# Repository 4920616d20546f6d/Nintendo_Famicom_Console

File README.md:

# Goals
This project documents the Nintendo Family Computer from Japan. The goal is to provide complete, verified, schematics and PCB for every version of the console and essential accessories.

# Progress
- December 1, HVC-CPU-GPM-02 all footprints reviewed. Holes and pads corrected. Revision uploaded.
- November 30, HVC-CPU-GPM-02 verified to be electrically correct. There are 3 mechanical errors. The drill sizes for the 15 pin connector, TC1, and Reset switch are too small. Drills and annulus will be adjusted in next revision.
- November 27, HVC-CPU-07 acquired
- November 12, 2025 the HVC-CPU-GPM-02 mainboard was sent out for manufacturing.
- November 10, 2025 the first versions of all essential hardware and accessories have been complete and added to the repository.

# Project Status
## Console HVC-001
| Revision | Schematic | Symbols | Datasheets | Notes | PCB | Footprint | Pads | Masks | Text | Graphics | Models | Photos | Ready for Manufacturer | Manufactured |
|----------|-----------|---------|------------|-------|-----|-----------|------|-------|------|----------|--------|--------|------------------------|--------------|
| HVC-CPU | ❌ | ❌ | ❌ | ❌ | ❌ | ❌ | ❌ | ❌ | ❌ | ❌ | ❌ | ❌ | ❌ | ❌ |
| HVC-CPU-02 | ❌ | ❌ | ❌ | ❌ | ❌ | ❌ | ❌ | ❌ | ❌ | ❌ | ❌ | ❌ | ❌ | ❌ |
| HVC-CPU-03 | ❌ | ❌ | ❌ | ❌ | ❌ | ❌ | ❌ | ❌ | ❌ | ❌ | ❌ | ❌ | ❌ | ❌ |
| HVC-CPU-04 | ❌ | ❌ | ❌ | ❌ | ❌ | ❌ | ❌ | ❌ | ❌ | ❌ | ❌ | ❌ | ❌ | ❌ |
| HVC-CPU-05 | ❌ | ❌ | ❌ | ❌ | ❌ | ❌ | ❌ | ❌ | ❌ | ❌ | ❌ | ❌ | ❌ | ❌ |
| HVC-CPU-06 | ❌ | ❌ | ❌ | ❌ | ❌ | ❌ | ❌ | ❌ | ❌ | ❌ | ❌ | ❌ | ❌ | ❌ |
| HVC-CPU-07 | ❌ | ❌ | ❌ | ❌ | ❌ | ❌ | ❌ | ❌ | ❌ | ❌ | ❌ | ❌ | ❌ | ❌ |
| HVC-CPU-GPM-01 | ❌ | ❌ | ❌ | ❌ | ❌ | ❌ | ❌ | ❌ | ❌ | ❌ | ❌ | ❌ | ❌ | ❌ |
| HVC-CPU-GPM-02 | ✔️ | ✔️ | ✔️ | ✔️ | ✔️ | ✔️ | ✔️ | ✔️ | ✔️ | ✔️ | ✔️ | ✔️ | ✔️ | ❗ |

## Controller 1
| Revision | Schematic | Symbols | Datasheets | Notes | PCB | Footprint | Pads | Masks | Text | Graphics | Models | Photos | Ready for Manufacturer | Manufactured |
|----------|-----------|---------|------------|-------|-----|-----------|------|-------|------|----------|--------|--------|------------------------|--------------|
| Mitsumi 56 8231 B | ✔️ | ✔️ | ❗ | ✔️ | ✔️ | ✔️ | ✔️ | ✔️ | ✔️ | ✔️ | ❗ | ✔️ | ✔️ | ❗ |

## Controller 2
| Revision | Schematic | Symbols | Datasheets | Notes | PCB | Footprint | Pads | Masks | Text | Graphics | Models | Photos | Ready for Manufacturer | Manufactured |
|----------|-----------|---------|------------|-------|-----|-----------|------|-------|------|----------|--------|--------|------------------------|--------------|
| Mitsumi 56 8232 A | ✔️ | ✔️ | ❗ | ✔️ | ✔️ | ✔️ | ✔️ | ✔️ | ✔️ | ✔️ | ❗ | ✔️ | ✔️ | ❗ |

## RF Modultaor
| Revision | Schematic | Symbols | Datasheets | Notes | PCB | Footprint | Pads | Masks | Text | Graphics | Models | Photos | Ready for Manufacturer | Manufactured |
|----------|-----------|---------|------------|-------|-----|-----------|------|-------|------|----------|--------|--------|------------------------|--------------|
| 1988 for HVC-CPU-GPM-02 | ✔️ | ✔️ | ❗ | ✔️ | ✔️ | ✔️ | ✔️ | ✔️ | ✔️ | ✔️ | ❗ | ✔️ | ✔️ | ❗ |

## AC Power Adaptor HVC-002
| Revision | Schematic | Symbols | Datasheets | Notes | PCB | Footprint | Pads | Masks | Text | Graphics | Models | Photos | Ready for Manufacturer | Manufactured |
|----------|-----------|---------|------------|-------|-----|-----------|------|-------|------|----------|--------|--------|------------------------|--------------|
| 1988 for HVC-CPU-GPM-02 | ✔️ | ✔️ | ❗ | ✔️ | ✔️ | ✔️ | ✔️ | ✔️ | ✔️ | ✔️ | ❗ | ✔️ | ✔️ | ❗ |

## RF Switch HVC-003
| Revision | Schematic | Symbols | Datasheets | Notes | PCB | Footprint | Pads | Masks | Text | Graphics | Models | Photos | Ready for Manufacturer | Manufactured |
|----------|-----------|---------|------------|-------|-----|-----------|------|-------|------|----------|--------|--------|------------------------|--------------|
| HVC-RFSW | ✔️ | ✔️ | ❗ | ✔️ | ✔️ | ✔️ | ✔️ | ✔️ | ✔️ | ✔️ | ❗ | ✔️ | ✔️ | ❗ |

# Links
https://github.com/emu-russia/breaks

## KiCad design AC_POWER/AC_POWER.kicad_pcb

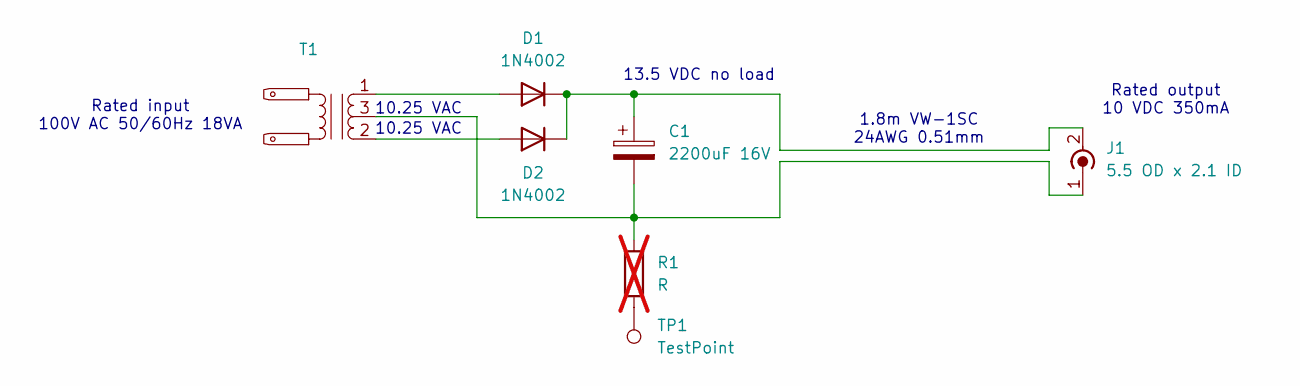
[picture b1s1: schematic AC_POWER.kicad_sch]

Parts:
C1: 2200uF 16V; capacitor
D1, D2: 1N4002; diode
J1: 5.5 OD x 2.1 ID; connector
R1: R; resistor; not fitted
T1: transformer
TP1: TestPoint; testpoint

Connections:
unnamed: D1.2 (A), T1.1
unnamed: C1.1, D1.1 (K), D2.1 (K), J1.2 (Ext)
unnamed: D2.2 (A), T1.2
unnamed: C1.2, J1.1 (In), R1.2, T1.3
unnamed: R1.1, TP1.1

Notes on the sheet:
Rated input 100V AC 50/60Hz 18VA
13.5 VDC no load
Rated output 10 VDC 350mA
1.8m VW-1SC 24AWG 0.51mm
10.25 VAC

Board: 2 copper layers, 7 parts (0 on the bottom side), 5 nets, no tracks yet.

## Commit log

2025-10-29 initial release
2025-10-29 Refactor schematic: * Move audio and video circuits to dedicated sheet * Move power and mechanical to dedicated sheet Modify P1 Cart Connector symbol to: * split out audio ports * organize pins for e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
2025-10-30 Change symbols to functional layout instead of pin map layout Add technical page to store pinouts Organize and compact root page
2025-10-30 Rearranged pins on some symbols to simplify schematic wiring Removed schematics for controller PCBs Added PNG version of schematics
2025-10-31 update font file with new glyphs
2025-10-31 Update most custom footprints to remove Silkscreen layer - Since the PCB was originally hand drawn, the silkscreen for the footprint, and other graphics is not consistent. - The silkscreen is removed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
2025-11-11 add Controller 1 and RF module schematics and PCBs
2025-11-11 clean up RF modulator schematic and PCB
2025-11-12 add AC POWER adapter
2025-11-12 add solder mask to PCB and clarify notes on schematic
2025-11-13 adding RF_SWITCH PCBs and schematics
2025-11-13 Update README with project summary and status tables
    Added project summary and detailed status tables for various components.
2025-11-13 Fix typo in project summary
    Corrected a typo in the README regarding 'verified'.
2025-11-15 Revise project goals and update status indicators
    Updated project goals and progress sections with recent milestones. Changed status indicators in project status tables to use symbols for clarity.
2025-11-27 annotate schematics, correct PCB/schematic parity issure, add datasheets
2025-11-27 add links to PPU and APU reverse engineering books
2025-11-27 Update README with progress and typo corrections
    Added new entries for HVC-CPU-07 and HVC-CPU-GPM-02 in the progress section. Included a new links section with a GitHub URL.
2025-12-01 Updated PCB and footprints to correct hole and pad sizes
2025-12-02 Update progress with December 1 review details
    Added a new progress update for December 1 regarding HVC-CPU-GPM-02.
2025-12-03 add PCB images for HVC-CPU-07
2025-12-06 Adding HVC-CPU-07 revision schematics and PCB layout
